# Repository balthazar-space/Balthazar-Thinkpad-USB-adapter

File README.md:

# Balthazar Thinkpad USB adapter

# About

This project will make a USB keyboard/Trackpoint controller and enclosure for the non-chiclet Thinkpad keyboard (from the 10/20 generation, such as the T410, W520, X230 etc.). 

[Keyboard 3](https://github.com/balthazar-space/Balthazar-Keyboard-3) and the Thinkpad over this adapter connect over a USB cable to the Balthazar Unifying board.

https://github.com/balthazar-space/Unifying-PCB

That will give users more options for customizations, and also the possibility to reuse some old Thinkpad keyboards.

You can also use this adapter to connect the Thinkpad keyboard on your PC,  connect the keyboard to the adapter, and use USBC for connection with your PC.

# Controller

The current plan is to use an RP2040 microcontroller running custom QMK to handle the key matrix scanning and Trackpoint.

# Project origin

Differences from the original project:

We have removed parts that the Balthazar Keyboard does not need.

We have removed the USB HUB on the board as we already have HUB on the unifying board. 

We only need one USB TYPE C connector, so we have removed the second one.

We have removed parts, and we made the PCB smaller.

Removing parts will lower production costs.

You can check the original project here: 

https://github.com/bluepylons/A-Thinkpad-USB-keyboard

Here you can find new [BOM](https://github.com/balthazar-space/Balthazar-Thinkpad-USB-adapter/tree/main/PCB/bom)

Adapter is stil not produced, but we should have some prototypes soon!

## License

CERN Open Hardware Licence Version 2 - Weakly Reciprocal

## Funding

This project is funded through the [NGI Zero Entrust Fund](https://nlnet.nl/entrust), a fund
established by [NLnet](https://nlnet.nl) with financial support from the European Commission's
[Next Generation Internet](https://ngi.eu) program. Learn more on the [NLnet project page](https://nlnet.nl/project/Balthazar-Casing/).

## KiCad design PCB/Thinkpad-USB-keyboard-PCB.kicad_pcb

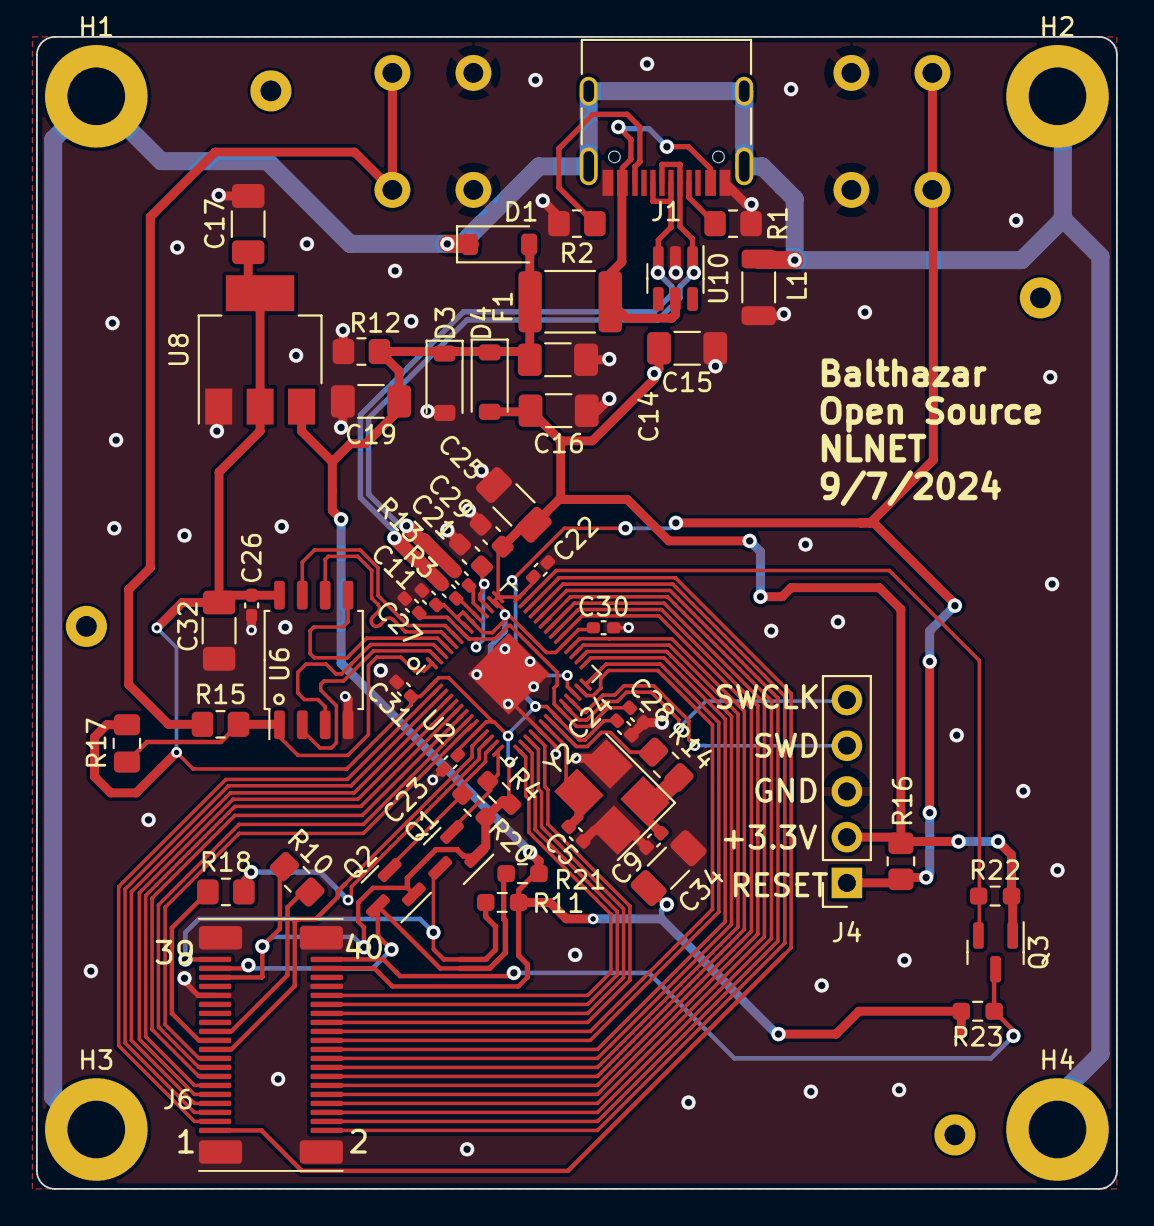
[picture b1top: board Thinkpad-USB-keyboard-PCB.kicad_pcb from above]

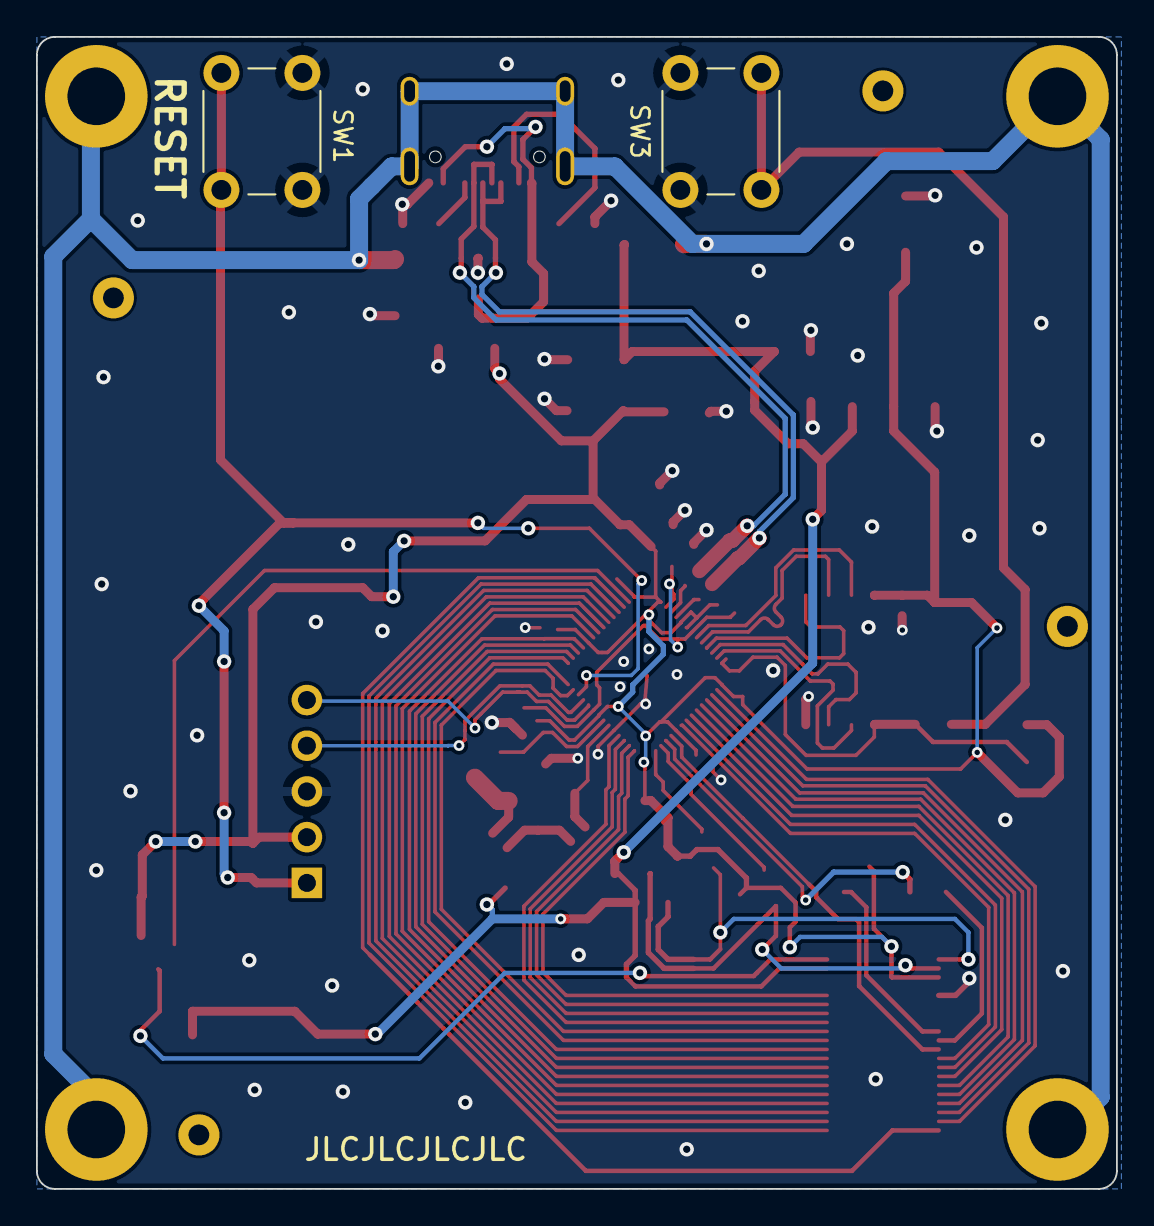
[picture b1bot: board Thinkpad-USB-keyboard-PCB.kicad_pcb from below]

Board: 4 copper layers, 60.0 x 64.0 mm, 64 parts (2 on the bottom side), 60 nets.

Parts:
C5, C9: 22pF; C_0402_1005Metric_Pad0.74x0.62mm_HandSolder
C11, C22, C23, C24, C26, C27, C28, C30, C31: 100nF; C_0402_1005Metric_Pad0.74x0.62mm_HandSolder
C14, C15, C16, C17, C19, C25, C32, C34: 10uF; C_1206_3216Metric_Pad1.33x1.80mm_HandSolder
C21, C29: 1uF; C_0603_1608Metric_Pad1.08x0.95mm_HandSolder
D1: SMF9.0CA; D_SOD-123
D3, D4: RB060M-60TR; D_SOD-123
F1: 1812L075PR; Fuse_1812_4532Metric_Pad1.30x3.40mm_HandSolder
H1, H2, H3, H4: MountingHole_Pad; MountingHole_3.2mm_M3_ISO7380_Pad
H9, H10, H11, H12: MountingHole; JLCPCB-tooling-hole
J1: USB_C_Receptacle_USB2.0; USB_C_Receptacle_HRO_TYPE-C-31-M-12
J4: SWD; PinSocket_1x05_P2.54mm_Vertical
J6: Conn_02x20_Odd_Even_MountingPin; Molex Slimstack 54363-0489
L1: 60R@100MHz; L_1206_3216Metric
Q1, Q2, Q3: BSS138; SOT-23
R1, R2: 5.1k; R_0805_2012Metric_Pad1.20x1.40mm_HandSolder
R3, R13: 27; C_0402_1005Metric_Pad0.74x0.62mm_HandSolder
R4, R11, R20, R21, R22, R23: 10K; R_0603_1608Metric_Pad0.98x0.95mm_HandSolder
R10, R18: 100; R_0805_2012Metric_Pad1.20x1.40mm_HandSolder
R12: 100k; R_0805_2012Metric_Pad1.20x1.40mm_HandSolder
R14, R15, R16: 1K; R_0805_2012Metric_Pad1.20x1.40mm_HandSolder
R17: DNI; C_0805_2012Metric_Pad1.18x1.45mm_HandSolder
SW1, SW3: SW_Push; SW_PUSH_6mm_H5mm
U2: RP2040; QFN-56-1EP_7x7mm_P0.4mm_EP3.2x3.2mm
U6: W25Q128JVS; SOIC-8_5.23x5.23mm_P1.27mm
U8: TLV1117-33; SOT-223-3_TabPin2
U10: SRV05-4; SOT-23-6
Y2: 12MHz; Crystal_SMD_3225-4Pin_3.2x2.5mm_HandSoldering

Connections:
+1V1: C21.1, C27.1, C28.1, U2.23 (DVDD), U2.45 (VREG_VOUT), U2.50 (DVDD)
+3V3: C11.1, C15.1, C16.1, C17.1, C22.1, C23.1, C24.1, C25.1, C26.1, C29.1, C30.1, C31.1, C32.1, D4.2 (A), J4.2, J6.35, Q1.1 (G), Q2.1 (G), Q3.1 (G), R4.2, R10.2, R16.2, R17.2, R20.2, R22.2, U2.1 (IOVDD), U2.10 (IOVDD), U2.22 (IOVDD), U2.33 (IOVDD), U2.42 (IOVDD), U2.43 (ADC_AVDD), U2.44 (VREG_IN), U2.48 (USB_VDD), U2.49 (IOVDD), U6.8 (VCC), U8.2 (VO)
+5V: C14.1, C19.1, C34.1, D1.2 (A2), D3.1 (K), D4.1 (K), F1.2, J6.38, R11.2, R12.2, R21.2, R23.2, U8.3 (VI)
/~USB_BOOT: R15.1, SW3.2
CS: R15.2, R17.1, U2.56 (QSPI_SS), U6.1 (~CS)
DRV0: J6.22, U2.28 (GPIO17)
DRV1: J6.18, U2.30 (GPIO19)
DRV2: J6.14, U2.32 (GPIO21)
DRV3: J6.10, U2.35 (GPIO23)
DRV4: J6.2, U2.39 (GPIO27_ADC1)
DRV5: J6.4, U2.38 (GPIO26_ADC0)
DRV6: J6.8, U2.36 (GPIO24)
DRV7: J6.12, U2.34 (GPIO22)
DRV8: J6.6, U2.37 (GPIO25)
DRV9: J6.20, U2.29 (GPIO18)
DRV10: J6.16, U2.31 (GPIO20)
DRV11: J6.24, U2.27 (GPIO16)
DRV12: J6.28, U2.17 (GPIO14)
DRV13: J6.32, U2.15 (GPIO12)
DRV14: J6.26, U2.18 (GPIO15)
DRV15: J6.30, U2.16 (GPIO13)
DUP+: J1.A6 (D+), J1.B6 (D+), R3.1, U10.3 (IO2)
DUP-: J1.A7 (D-), J1.B7 (D-), R13.1, U10.1 (IO1)
GND: C5.1, C9.1, C11.2, C14.2, C15.2, C16.2, C17.2, C19.2, C21.2, C22.2, C23.2, C24.2, C25.2, C26.2, C27.2, C28.2, C29.2, C30.2, C31.2, C32.2, C34.2, D3.2 (A), J1.A1 (GND), J1.A12 (GND), J1.B1 (GND), J1.B12 (GND), J4.3, J6.31, J6.34, J6.MP (MountPin), L1.1, R1.2, R2.2, R12.1, SW1.1, SW3.1, U2.19 (TESTEN), U2.57 (GND), U6.4 (GND), U8.1 (GND), U10.2 (VN), Y2.2, Y2.4
GNDPWR: D1.1 (A1), H1.1, H2.1, H3.1, H4.1, J1.S1 (SHIELD), L1.2
HOTKEY: J6.1, U2.40 (GPIO28_ADC2)
LED-CAPS-LOCK: J6.21, R18.1
LED-POWER: J6.23, R10.1
unnamed: C9.2, R14.1, Y2.1
unnamed: J1.A5 (CC1), R1.1
unnamed: J1.B5 (CC2), R2.1
unnamed: R18.2, U2.12 (GPIO9)
unnamed: R13.2, U2.46 (USB_DM)
unnamed: R3.2, U2.47 (USB_DP)
unnamed: C5.2, U2.20 (XIN), Y2.3
unnamed: R14.2, U2.21 (XOUT)
PWRSWITCH: J6.19, U2.11 (GPIO8)
QSPI_CLK: U2.52 (QSPI_SCLK), U6.6 (CLK)
RESET: J4.1, R16.1, SW1.2, U2.26 (RUN)
SD0: U2.53 (QSPI_SD0), U6.5 (DI(IO0))
SD1: U2.55 (QSPI_SD1), U6.2 (DO(IO1))
SD2: U2.54 (QSPI_SD2), U6.3 (IO2)
SD3: U2.51 (QSPI_SD3), U6.7 (IO3)
SENSE0: J6.5, U2.3 (GPIO1)
SENSE1: J6.13, U2.7 (GPIO5)
SENSE2: J6.9, U2.5 (GPIO3)
SENSE3: J6.7, U2.4 (GPIO2)
SENSE4: J6.11, U2.6 (GPIO4)
SENSE5: J6.3, U2.2 (GPIO0)
SENSE6: J6.15, U2.8 (GPIO6)
SENSE7: J6.17, U2.9 (GPIO7)
SWCLK: J4.5, U2.24 (SWCLK)
SWD: J4.4, U2.25 (SWD)
TP4-CLK-3V3: Q1.2 (S), R4.1, U2.14 (GPIO11)
TP4-CLK-5V: J6.39, Q1.3 (D), R11.1
TP4-DATA-3V3: Q2.2 (S), R20.1, U2.13 (GPIO10)
TP4-DATA-5V: J6.37, Q2.3 (D), R21.1
TP4-RESET-3V3: Q3.2 (S), R22.1, U2.41 (GPIO29_ADC3)
TP4-RESET-5V: J6.40, Q3.3 (D), R23.1
VBUS: F1.1, J1.A4 (VBUS), J1.A9 (VBUS), J1.B4 (VBUS), J1.B9 (VBUS), U10.5 (VP)

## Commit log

2024-07-11 Balthazar Thinkpad USB adapter v1.0
2024-07-14 Updating README
